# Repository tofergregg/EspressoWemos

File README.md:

README.md file for EspressoWemos

The files here are in version 0.1 shape -- they work on my machine and setup, and I don't expect anyone to be able to drop this into their own setup without some modifications.

I will amend this file when I have a chance to explain more about the project and how it works, and to give more details.

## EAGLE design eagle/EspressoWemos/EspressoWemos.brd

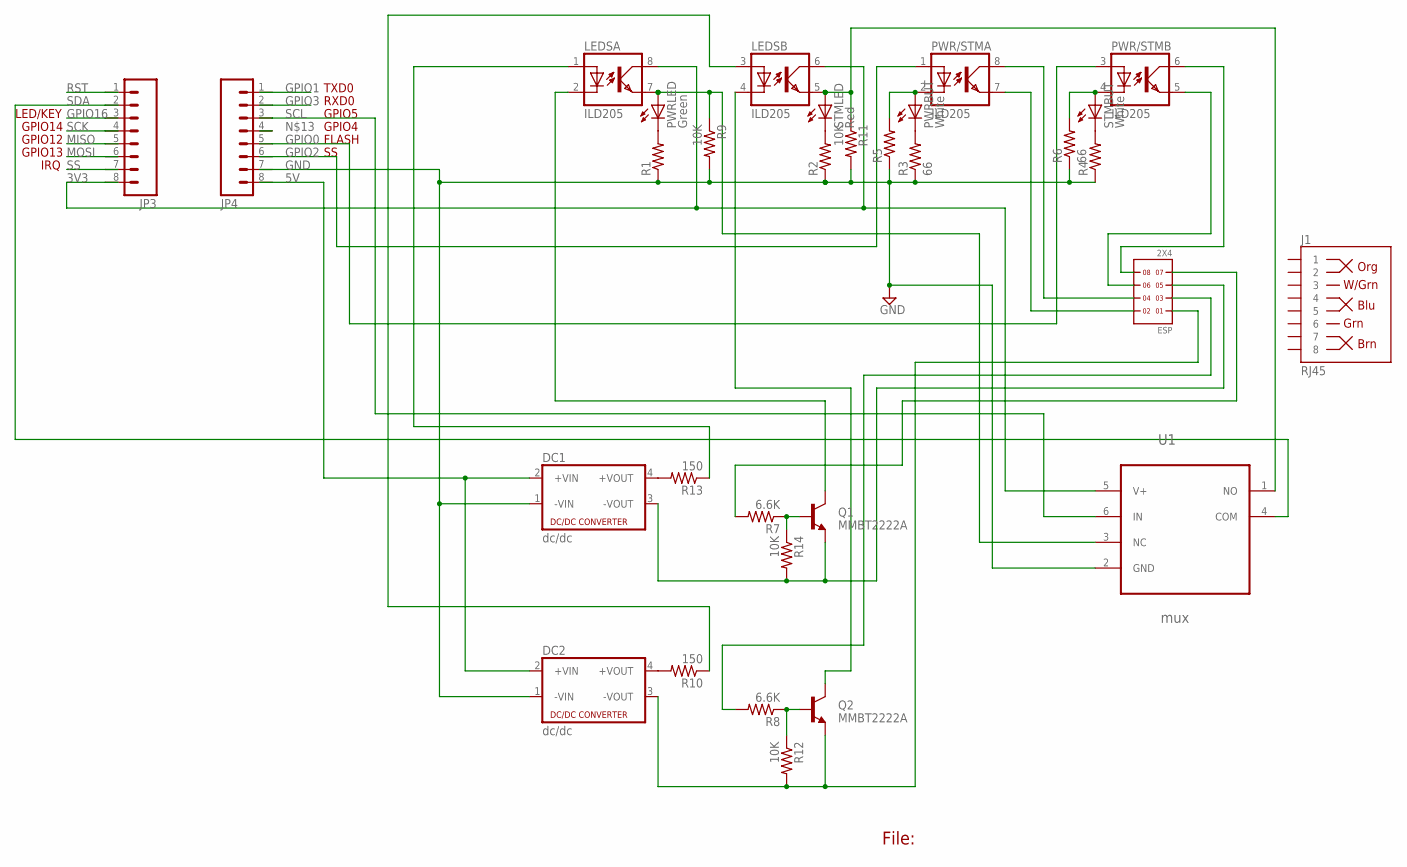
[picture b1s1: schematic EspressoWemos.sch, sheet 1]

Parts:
DC1, DC2: dc/dc; 4SIL
ESP: 2X4
J1: RJ45; RJ45-8
JP3, JP4: M08NO_SILK_FEMALE_PTH; 1X08_NO_SILK
LEDS: ILD205; SOIC08
PWR/STM: ILD205; SOIC08
PWRBUT: White; SML1206
PWRLED: Green; SML1206
Q1, Q2: MMBT2222A; SOT23-3
R1, R2, R4, R5: R-US_R1206; R1206
R3, R6: 66; R1206
R7, R8: 6.6K; R1206
R9, R11, R12, R14: 10K; R1206
R10, R13: 150; R1206
STMBUT: White; SML1206
STMLED: Red; SML1206
U1: mux; SOT95P280X145-6N

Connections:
3V3: JP3.8, LEDS.6 (COL), LEDS.8 (COL), U1.5 (V+)
5V: DC1.2 (+VIN), DC2.2 (+VIN), JP4.8
GND: DC1.1 (-VIN), DC2.1 (-VIN), JP4.7, R1.1, R2.1, R3.1, R4.1, R5.1, R6.1, R9.2, R11.2, U1.2 (GND)
GPIO0: JP4.5, PWR/STM.3 (A)
GPIO1: JP4.1
GPIO2: JP4.6, PWR/STM.1 (A)
GPIO3: JP4.2
GPIO16: JP3.3
MISO: JP3.5
MOSI: JP3.6
unnamed: PWRLED.C, R1.2
unnamed: R2.2, STMLED.C
unnamed: ESP.2, PWR/STM.7 (EMIT)
unnamed: PWRBUT.C, R3.2
unnamed: ESP.6, PWR/STM.5 (EMIT)
unnamed: R4.2, STMBUT.C
unnamed: ESP.4, PWR/STM.8 (COL)
unnamed: ESP.8, PWR/STM.6 (COL)
unnamed: PWR/STM.2 (C), PWRBUT.A, R5.2
unnamed: PWR/STM.4 (C), R6.2, STMBUT.A
unnamed: LEDS.7 (EMIT), PWRLED.A, R9.1, U1.3 (NC)
unnamed: ESP.7, R7.2
unnamed: LEDS.2 (C), Q1.3 (C)
unnamed: LEDS.5 (EMIT), R11.1, STMLED.A, U1.1 (NO)
unnamed: ESP.3, R8.2
unnamed: Q1.1 (B), R7.1, R14.1
unnamed: Q2.1 (B), R8.1, R12.1
unnamed: DC1.4 (+VOUT), R13.2
unnamed: DC2.4 (+VOUT), R10.2
unnamed: DC2.3 (-VOUT), ESP.1, Q2.2 (E), R12.2
unnamed: LEDS.1 (A), R13.1
unnamed: LEDS.3 (A), R10.1
unnamed: DC1.3 (-VOUT), ESP.5, Q1.2 (E), R14.2
unnamed: LEDS.4 (C), Q2.3 (C)
RST: JP3.1
SCK: JP3.4
SCL: JP4.3, U1.6 (IN)
SDA: JP3.2, U1.4 (COM)
SS: JP3.7

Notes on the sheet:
File:
FLASH
GPIO12
GPIO4
GPIO5
RXD0
TXD0
GPIO13
GPIO14
IRQ
LED/KEY

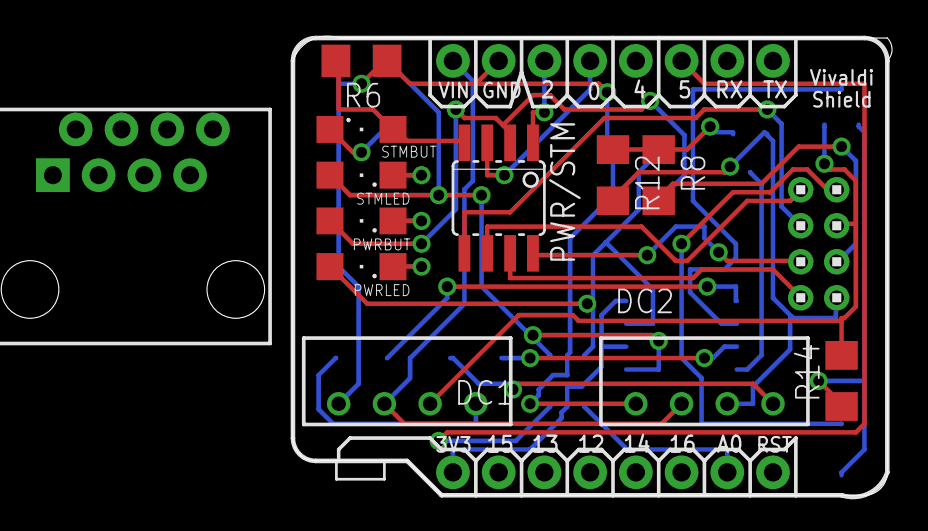
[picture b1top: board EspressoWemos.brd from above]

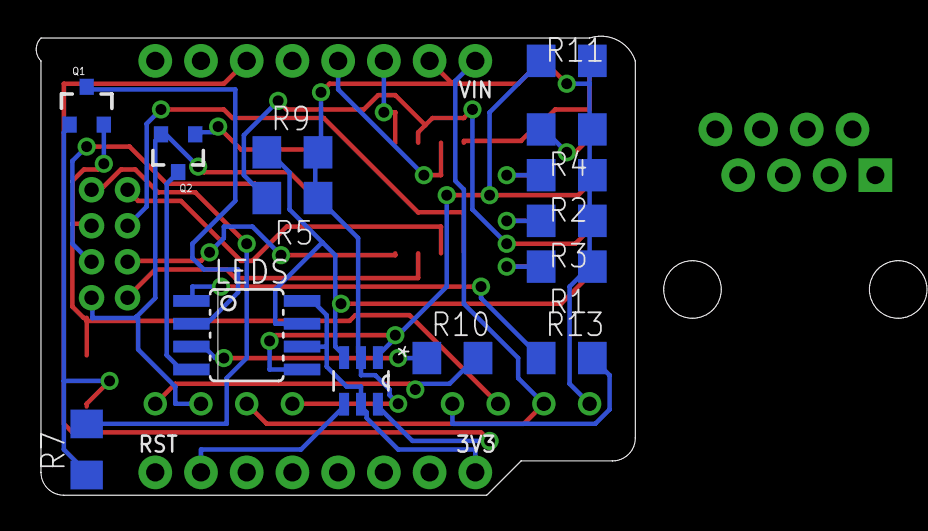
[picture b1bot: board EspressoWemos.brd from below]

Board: 2 copper layers, 33.3 x 25.5 mm, 29 parts (14 on the bottom side), 31 nets.

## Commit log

2016-06-01 Added eagle files
2016-08-04 Updated eagle files
2016-08-04 Added Intime files
2016-08-09 Added arduino files
2016-08-09 removed server files to rename
2016-08-09 Added server files back again
2017-10-11 updated .ino file

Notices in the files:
parts and their libraries:
SparkFun-Connectors: Licensing: Creative Commons ShareAlike 4.0 International - https://creativecommons.org/licenses/by-sa/4.0
